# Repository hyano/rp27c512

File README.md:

# RP27C512

**RP27C512**は、[秋月電子通商](https://akizukidenshi.com/)の
[RP2040マイコンボードキット(AE-RP2040)](https://akizukidenshi.com/catalog/g/g117542/)を使用して、
EP-ROM(27C512)のエミュレーションを行うデバイスです。
このデバイスは、AE-RP2040のGPIOを27C512相当のDIP-28ピンアサインに変換する基板と、GPIOを制御するためのファームウェアで構成されています。

ROMのエミュレーションに加え、同一バス上のメモリやデバイスへのアクセスを監視・解析する機能も備えていることが特長です。

ROMデータ書き換えて機器やプログラムの動作確認をしたり、
メモリの内容やデバイスのアクセスを監視して機器の挙動を調べる用途を想定しています。

興味のある方がいらっしゃれば、基板やキットの頒布を検討しますので、お声掛けください。

## 概要

* 27C512の代わりに**RP27C512**を装着して、ROM機能をエミュレーションすることができます。
* /OE信号がアサートされてから約40nsでデータ出力が可能です。
* **RP27C512**をホスト(Windows PCやMac)に接続すると、USBシリアルポートとして認識されます。
* UARTターミナルを使って、コマンドラインインターフェースから各種操作が可能です。
* ROMデータはAE-RP2040のフラッシュメモリに最大4つまで保存でき、切り替えて使用できます。
* ホストからROMデータを**RP27C512**に転送できます。転送にはXMODEMを使用します。
* **RP27C512**に保存されたROMデータをホストに転送することが可能です。転送にはXMODEMを使用します。
* **RP27C512**をROM(27C512)に接続し、実チップからデータを直接読み出すことができます。
* **RP27C512**の基板を流用して、ROM(27C512)を**RP27C512**に接続するための子基板を作ることができます。
* バスアクセスの監視機能を備えており、同一バス上に接続されたメモリやデバイスへのアクセスを解析できます。
  * 書き込みデータを**RP27C512**のRAMに記録して、確認できます。機器のRAMの内容に相当します。
  * RAMのデータをXMODEMを使用してホストとの間で転送することが可能です。
  * 指定した領域へのアクセスを時系列で表示することができます。
* 3つの動作モードを備えます。
  * emulatorモード: ROMのエミュレーションとバスアクセスの監視をします。
  * snoopモード: バスアクセスの監視をします。
  * cloneモード: ROMの読み出しをします。

## ハードウェア

* [RP27C512/AE-RP2040変換基板](hardware/)は、AE-RP2040のピンアサインを27C512相当に変換するシンプルな基板です。
* 回路図や基板レイアウトはKiCadで作成しており、`hardware/`ディレクトリに格納しています。
* **<ins>AE-RP2040のGPIOは3.3Vで、27C512は5Vで駆動しますが、レベル変換回路は入れていません。
  作者の環境では正常に動作していますが、故障や想定外の動作について作者は責任を負いかねます。</ins>**
* RP2040を400MHzまでオーバークロックして使用しています。
* 27C512側の5V電源をAE-RP2040に供給することが可能です。ショットキーバリアダイオードで逆流防止を行っています。

### 信号の接続関係

|AE-RP2040|接続先|信号名|補足                             |
|---------|------|------|---------------------------------|
|GPIO0-15 |27C512|A0-15 |アドレスバス                     |
|GPIO16-23|27C512|DQ0-7 |データバス                       |
|GPIO27   |27C512|/CE   |チップイネーブル                 |
|GPIO28   |27C512|/OE   |出力イネーブル                   |
|GPIO29   |基板  |/WR   |4Pピンヘッダ1/書き込みイネーブル |
|GPIO24   |-     |(EXT0)|4Pピンヘッダ2/将来用             |
|GPIO25   |-     |(EXT1)|4Pピンヘッダ3/将来用             |
|GPIO26   |-     |(EXT2)|4Pピンヘッダ4/将来用             |
|GND      |27C512|VSS   |                                 |
|+5V      |27C512|VCC   |ショットキーバリアダイオード経由 |
|+3.3V    |-     |-     |                                 |

### 部品一覧

[RP27C512/AE-RP2040変換基板](hardware/)の他に必要になる部品の一覧です。
[秋月電子通商](https://akizukidenshi.com/)で揃える場合の例です。電気的に接続するだけなので、同等品で問題ありません。
子基板はsnoopモードとcloneモードでROMを接続しやすくするためのもので、ROMエミュレーションには必要ありません。

* 親基板(本体)
  * [RP2040マイコンボードキット](https://akizukidenshi.com/catalog/g/g117542/)
  * [ロープロファイルピンヘッダー(低オス) 1×40(40P) 9.54mm](https://akizukidenshi.com/catalog/g/g100171/)
    * 子基板を取り付けない場合は
      [ロープロファイルピンヘッダー(低オス) 1×40(40P) 7.7mm](https://akizukidenshi.com/catalog/g/g102900/)
      の方が見栄えがよいでしょう。
  * [丸ピンIC用連結ソケット 1×14 MH-1X14-L2](https://akizukidenshi.com/catalog/g/g116982/)
    * 秋葉原の店舗には常備していないようなので要注意です。
    * [丸ピンIC用連結ソケット 両端オスピン・1列14P](https://akizukidenshi.com/catalog/g/g100862/)のピンを切断して使っても、
      [細ピンヘッダー 1×40 (黒)](https://akizukidenshi.com/catalog/g/g106631/)を使ってもよいでしょう。
  * [ピンヘッダー (オスL型) 1×40 (40P)](https://akizukidenshi.com/catalog/g/g101627/)
  * [ショットキーバリアダイオード 45V2A SBM245L](https://akizukidenshi.com/catalog/g/g117439/)
    * 適当なもので構わないです。VFの小さな安価なものを使いました。
* 子基板(snoopモード・cloneモード用)
  * [シングルピンソケット (低メス) 1×20 (20P)](https://akizukidenshi.com/catalog/g/g103138/)
  * [ICソケット (28P) 600mil](https://akizukidenshi.com/catalog/g/g115763/)
  * スズメッキ線少々
    * 親基板のダイオードのリード線の残りなどで問題ないでしょう。

### 組み立て(親基板)

各部品を部品を基板にハンダ付けして取り付けます。
スペースが狭く、干渉するので、ハンダの量が多くなりすぎないように注意します。

* ショットキーバリアダイオードを基板に取り付けます。
  * USBケーブルからの電源のみで使用する場合は、必要はありません。
  * ダイオードの太さによってはAE-RP2040と接触します。作者は気にしていません。
* 丸ピンIC用連結ヘッダを基板に取り付けます。
  * ロープロファイルピンヘッダーとの距離が狭いため、両方を基板に固定した状態でハンダ付けするとよいです。
* ロープロファイルピンヘッダーを基板に取り付けます。
  * 9.54mmタイプを使用する場合は、足の長いピンが上方(AE-RP2040側)になる向きにします。
* L型ピンヘッダーを4P分に切断し、基板に取り付けます。
  * 先に取り付けてしまうと、樹脂部分が邪魔で、丸ピンIC用連結ヘッダの半田付けが難しくなります。
* ロープロファイルピンヘッダーにAE-RP2040を取り付けます。
  * 基板間が狭いので、スペースを残すためにQIコネクタを取り付けた状態でハンダ付けするとよいです。
  * 子基板を使用する場合、ハンダが上方に付着していると子基板のピンソケットに刺さりません。
    スルーホール付近にだけハンダが乗るようにします。多くつき過ぎた場合は、ハンダ吸い取り線で除去するのがよいです。

### 組み立て(子基板)

snoopモードとcloneモードでROMを接続しやすくするための基板です。

* スズメッキ線をダイオードの代わりにD1の位置に取り付けます。
* ICソケットを取り付けます。
  * 次に取り付けるシングルピンソケットも基板に固定した状態でハンダ付けするとよいです。
* シングルピンソケットを17P分に切断し、基板に取り付けます。

## ファームウェア

* このプログラムは[Raspberry Pi Pico-series C/C++ SDK](https://www.raspberrypi.com/documentation/pico-sdk/)でビルド可能です。
* ソースコードは`firmware/`ディレクトリに格納しています。
* ビルド後に生成される`rp27c512.uf2`を所定の方法で**RP27C512**に書き込み、使用します。

## ファームウェアのビルド

事前に Raspberry Pi Pico SDK をインストールし、下記のコマンドでビルドすることができます。

```sh
git clone https://github.com/hyano/rp27c512.git
cd rp27c512/firmware
mkdir build
cd build
cmake ..
make
cp rp27c512.uf2 /Volumes/RPI-RP2
```

## 使用方法

### ハードウェアの取り付け

* emulatorモードで使用する場合、基板のICソケットからROM(27C512)を外し、代わりに**RP27C512**を取り付けます。その他のモード、詳細は、以降の各モードの説明を参照して下さい。
* 書き込みアクセスをキャプチャする場合は、基板下側の4Pピンヘッダのうち、シルクが白く塗りつぶされたピンを/WR信号に接続します。
* ホストとUSBケーブルで接続すると、USBシリアルポートとして認識されます。
* USBケーブルを接続しなくても基板側の電源で動作しますが、**RP27C512**の起動時間が必要なため、接続先の機器の起動に間に合わないかもしれません。
* 基板下側のピンヘッダの残り3Pは将来拡張用です。他の信号キャプチャや、機器のリセットなどの制御に使用することを検討しています。

### コマンドラインインタフェース

**RP27C512**をホストとUSBケーブルで接続すると、USBシリアルポートとして認識されます。
UARTターミナルを使って、コマンドラインインターフェースから各種コマンドを使用して操作することができます。

|コマンド|引数|説明|モード|
|-|-|-|-|
|help, ?|-|ヘルプを表示する。|e/s/c|
|hello|any...|コマンドラインの動作確認用。与えられた引数を表示する。|e/s/c|
|cls|-|画面をクリアする。|e/s/c|
|reboot|[delay]|再起動する。delayで再起動までの秒数を指定可能。|e/s/c|
|mode|"emulator"\|"snoop"\|"clone"|ROMエミュレーションを行うemulatorモード、アクセスの解析のみを行うsnoopモード、ROMの読み出しを行うcloneモードを切り替える。modeはFLASH ROMに保存される。コマンド実行完了後、自動的に再起動する。|e/s/c|
|bootsel|[delay]|RP2040をBOOTSELモードで再起動する。|e/s/c|
|gpio|-|GPIOの状態と設定を表示する。|e/s/c|
|gpio|"in"\|"out" pin|GPIOを入力か出力を設定する。(ext0-2のみに有効)|e/s/c|
|gpio|"pullup"\|"pulldown"\|"pullno" pin|GPIOをプルアップ/プルダウン/どちらもなしを設定する。|e/s/c|
|gpio|"set"\|"clr" pin|GPIOの値を設定する。(ext0-2のみに有効)|e/s/c|
|gpio|"pulse" pin [width]|GPIOの値を一定期間反転する。width[us]でパルス幅を指定する(defaultは100us)。(ext0-2のみに有効)|e/s/c|
|gpio|"save"|FLASH ROMにGPIOの設定を保存する。|e/s/c|
|device|"rom"\|"ram"|操作対象のデバイスをROMかRAMで切り替える。ダンプ、データ転送に影響する。|e/s/-|
|d|[addr]|デバイス上のデータを指定したアドレスから16進ダンプする。アドレスを省略すると前回の続きをダンプする。|e/s/c|
|dw|[addr]|何かキーが押されるまで、16進ダンプを繰り返す。RAM上のデータの変化を目視するために使う。|e/s/-|
|dlen|len ["save"]|16進ダンプする時の表示行数を設定する。数値の後にsaveオプションをつけると設定をFLASH ROMに保存する。|e/s/c|
|e|[addr [value]]|デバイス上のデータを編集する。アドレスを省略すると前回の続きを編集する。値を省略すると対話型で入力になる。|e/s/c|
|m|start end dest|デバイス上のデータを移動する。|e/s/c|
|f|start end value|デバイス上の指定範囲を指定した値で埋める。|e/s/c|
|watch|start end|指定したアドレス範囲をcapコマンドでキャプチャするよう設定する。|e/s/-|
|unwatch|start end|指定したアドレス範囲をcapコマンドでキャプチャしないよう設定する。|e/s/-|
|cap|-|設定したアドレス領域へのアクセスを時系列に従って表示する。|e/s/-|
|wlist|[start [end]]|capコマンドでキャプチャする範囲を表示する。start、endで表示する範囲を指定できる。|e/s/-|
|wsave|-|capコマンドでキャプチャする範囲を保存する。|e/s/-|
|recv|-|ホストからデバイスにデータを転送する。64KiBのバイナリデータをXMODEM(CRC)で転送する。|e/s/c|
|send|-|デバイスからホストにデータを転送する。64KiBのバイナリデータをXMODEM(1K)で転送する。|e/s/c|
|bank|0\|1\|2\|3|使用するFLASH ROMのバンクを指定する。バンクの指定はFLASH ROMに保存され、次回起動時はそのバンクからROMデータを読み出す。|e/s/c|
|load|-|FLASH ROMからデータを読み出す。bankコマンドで指定したバンクを使用する。|e/s/c|
|save|-|FLASH ROMにデータを保存する。bankコマンドで指定したバンクを使用する。|e/s/c|
|erase|0\|1\|2\|3|FLASH ROMのデータを消去する。バンク番号を明示的に指定する。|e/s/c|
|clone|[wait [verify]]|直接接続した27C512からデータを読み出す。読み出し開始までの秒数(wait)と、ベリファイ回数(verify)を指定できる。|-/c|
|init|"all"\|"rom"\|"config"|FLASH ROMのデータ、設定を初期化する。設定を初期化する場合は、自動的に再起動する。|e/s/c|

* モードはe(emulatorモード)、s(snoopモード)、c(cloneモード)を示します。
* [arg]は省略可能な引数を表します。
* FLASH ROMにアクセスするコマンドを実行すると、動作クロック周波数を一時的に下げるためにROMエミュレーションが乱れます。
* gpioコマンドのピン指定は番号の他に信号名も使えます。(a0-a15,d0-d7,ce,oe,wr,ext0-ext2)
* 引数のチェックはほとんどしていないので、不正な引数を指定するとすぐに暴走します。

### emulatorモード

emulatorモードは、**RP27C512**をROM(27C512)の代わりに動作させるモードです。
`mode emulator`コマンドでemulatorモードに切り替わります。

emulatorモードでは、ROMを基板のICソケットから取り外し、代わりに**RP27C512**を取り付けます。
ROMが基板直付けの場合は、ICソケットを取り付けると良いでしょう。

書き込みアクセスをキャプチャするには、基板下側の4Pピンヘッダのうち、シルクが白く塗りつぶされたピンを/WR信号に接続します。

**RP27C512**の起動時にFLASH ROMからROMデータが読み出され、すぐにROMのエミュレーションが開始されます。

ROMデータは、USBターミナルソフトからXMODEMで転送するか、後述のcloneモードで実チップから読み出すかで、
あらかじめ**RP27C512**のFLASH ROMに保存しておきます。
FLASH ROMアクセス中は、**RP27C512**の動作クロック周波数を下げる必要があるため、ROMのエミュレーション速度が落ちます。
基板から取り外すか、基板の電源を切った状態で作業すると良いでしょう。

### snoopモード

snoopモードは、emulatorモードからROMのエミュレーションを停止させたモードです。
オリジナルのROMを使いつつ、バスのアクセスを監視する場合に使います。
`mode snoop`コマンドでsnoopモードに切り替わります。

snoopモードでは、ROMと基板の間に**RP27C512**を取り付けます。
**RP27C512**に子基板を取り付け、そのICソケットにオリジナルのROMを取り付けると良いでしょう。

### cloneモード

cloneモードは、**RP27C512**を直接ROM(27C512)の実チップに接続して、データを読み出すモードです。
`mode clone`コマンドでcloneモードに切り替わります。

子基板を使用する場合は、子基板にROMを取り付け、子基板を**RP27C512**に上から接続します。
ROMの電源はUSBポートから供給されます。

子基板を使用しない場合は、ROMに上から被せる形で**RP27C512**を乗せ、ピン同士を接触させます。
**RP27C512**を直接被せるのではなく、平ピン型のICソケットを間に挟むと、より接触させやすいです。
ROMの電源は外部から供給しても良いですし、**RP27C512**のショットキーバリアダイオードをバイパスしてUSBポートから供給しても良いでしょう。

接続ができたら、`clone`コマンドで実チップからデータを読み出します。
読み出しに成功したら、`save`コマンドでFLASH ROMに保存して、`mode emulator`でemulatorモードに戻しておきます。

**RP27C512**内のROMデータは、XMODEMでホスト側に転送することもできますので、簡易ROMリーダとしても使用することができます。

```sh
> mode clone
mode: clone
rebooting...

connected.
RP27C512 VER1.00
rom bank: 0
mode: clone
> clone
read ROM
 wait  : 5 s
 verify: 2 times
read start ... done.
verify (1/2) ... OK
verify (2/2) ... OK
clone: OK
> bank 0
current rom bank: 0
> save
save: OK
> mode emulator
mode: emulator
rebooting...

connected.
RP27C512 VER1.00
rom bank: 0
mode: emulator
> 
```

## ROMエミュレーションの実装

ROMエミュレーションは、データ出力部とバス制御部から構成されます。
アドレスバス(A0-A15)と制御信号(, /OE)の状態に応じて、データバス(D0-D7)に値を出力します。

### データ出力部

データ出力部は、アドレスバス(A0-A15)で指定されたアドレスに対応するROMイメージのデータを、データバス(D0-D7)に設定します。
PIOステートマシン1つ(SM)と、DMAを2チャネル(DMA0, DMA1)使用して実現しています。

* SMには、ROMイメージの配列変数の先頭アドレスの上位16ビットを転送して初期化します。
  * ROMイメージの配列変数は64KiBにアラインメントしておきます。
* SMは、GPIO(A0-A15)を読み出し、アクセス先のアドレスを合成し、FIFOに送信します。
* DMA0はSMのFIFOを監視するように設定しておき、SMからアドレスが送られてきたら、DMA1にそのアドレスからデータ転送を指示します。
* DMA1は、DMA0から指示されたアドレスからデータを読み出し、SMのFIFOに書き込みます。
* SMはDMA1から送られてきたデータをGPIO(D0-D7)に出力します。
* 上記を繰り返します。

### バス制御部

バス制御部は、制御信号(/CE, /OE)を監視し、データバス(D0-D7)を出力状態を制御します。
PIOステートマシン1つで実現しています。

* SMは、GPIO(/CE, /OE)の値を確認します。
* 両方が0の場合は、GPIO(D0-D7)を出力モードに切り替えます。
* そうでない場合は、GPIO(D0-D7)を入力モード(ハイインピーダンス)に切り替えます。
* 上記を繰り返します。

## バスアクセス監視の実装

バスアクセス監視は、書き込みデータ取り込み部とアクセスデータキャプチャ部から構成されます。

### 書き込みデータ取り込み部

書き込みデータ取り込み部は、書き込みアクセスがあると、アドレスバス(A0-A15)で指定されたRAMイメージのアドレスに、
データバス(D0-D7)の値を書き込みます。
PIOステートマシン1つ(SM)とDMAを2チャネル(DMA0, DMA1)使用して実現しています。

* SMには、ROMイメージの配列変数の先頭アドレスの上位16ビットと、
  0~256をあらかじめ書き込んだ値データの配列変数の先頭アドレスの上位24ビットを転送して初期化します。
  * RAMイメージの配列変数は64KiBにアラインメントしておきます。
  * 値データの配列変数は256Bにアラインメントしておきます。
* SMは、GPIO(/WR)の立ち上がりを待ち、その時のGPIOの値をキャプチャします。
* SMは、GPIO(D0-D7)の値から値データのアドレスを合成し、FIFOに送信します。
* SMは、GPIO(A0-A15)の値からRAMアクセス先のアドレスを合成し、FIFOに送信します。
* DMA0はSMのFIFOを監視するように設定しておき、SMからアドレス二つが送られてきたら、DMA1にそのアドレス間のデータ転送を指示します。
* DMA1は、DMA0から指示された値データのアドレスからデータを読み出し、RAMイメージのアドレスに書き込みます。
* 上記を繰り返します。

### アクセスデータキャプチャ部

アクセスデータキャプチャ部は、制御信号(/WR, /OE)を監視し、変化があるとその内容を64エントリのリングバッファに取り込みます。
PIOステートマシン1つ(SM)とDMAを2チャネル(DMA0, DMA1)使用して実現しています。

* SMは、GPIO(/WR, /OE)を確認します。
* 両方が1に変化した時、その時のGPIO(A0-A15, D0-D7, EXT0-EXT2, /CE)の値と直前のGPIO(/WR, /OE)の値を合成して、FIFOに送信します。
* DMA1は、SMから送られてきたデータをリングバッファに書き込みます。
  * リングバッファは、256Bにアラインメントしておきます。
  * リングバッファのどこまで書き込んだかは、DMAの書き込み先アドレスを確認することで知ることができます。
* リングバッファの終端に到達すると、DMA1は転送を終了して、DMA0をトリガします。
* DMA0は、DMA1の転送先アドレスをリングバッファの先頭に設定して、DMA1を再起動します。
* 上記を繰り返します。

## デモ動画

Roland CM-32PのROMを**RP27C512**で置き換え、
X68000版 闇の血族(1990 システムサコム)のBGM(CM-64向け)を演奏した時のRAMの内容のダンプ、
PCMデバイスへのアクセスの監視をしている様子をデモとして録画したものです。

https://github.com/user-attachments/assets/20a8eae4-5df2-4a57-8465-a8b28be44191

## 注意事項

* 作者の手元のごく少数の機器でのみ動作確認しています。すべての機器での動作を保証することはできません。
* 作者は、本デバイスの使用による一切の損害について責任を負いかねます。使用は使用者の責任で行ってください。

## 利用しているオープンソースソフトウェア

* [XMODEM implementation](https://github.com/Thuffir/xmodem)
  * Copyright 2001-2019 Georges Menie (www.menie.org)
  * Modified by Thuffir in 2019
* [Micro Read Line library for small and embedded devices with basic VT100 support](https://github.com/dimmykar/microrl-remaster)
  * Author: Eugene Samoylov aka Helius (ghelius@gmail.com) 01.09.2011
  * Remastered by: Dmitry Karasev aka dimmykar (karasevsdmitry@yandex.ru) 27.09.2021

## 参考文献・ソフトウェア

* [PicoROM: An RP2040-based ROM emulator](https://github.com/wickerwaka/PicoROM)
* [picoROM_pio: PIO/DMA implementation of picoROM project to simulate an EEPROM using a Raspberry Pico](https://github.com/rhulme/picoROM_pio)
* [Raspberry Pi Pico-series C/C++ SDK](https://datasheets.raspberrypi.com/pico/raspberry-pi-pico-c-sdk.pdf)
* [RP2040 Datasheet](https://datasheets.raspberrypi.com/rp2040/rp2040-datasheet.pdf)

## ライセンス

このソフトウェアは[MITライセンス](LICENSE)にて提供しています。  
Copyright (c) 2024 Hirokuni Yano

利用しているオープンソースソフトウェアは、そのライセンスに従います。

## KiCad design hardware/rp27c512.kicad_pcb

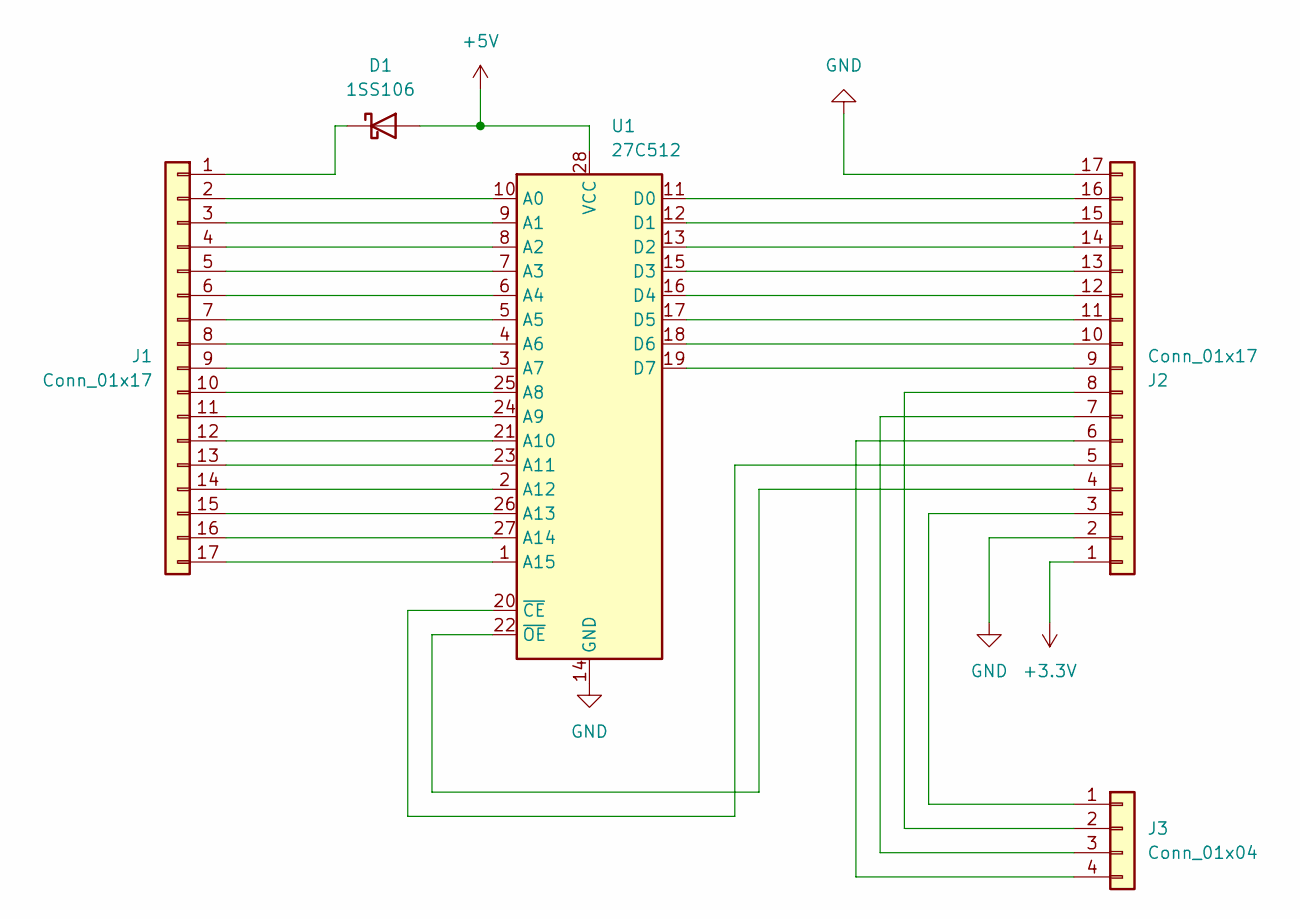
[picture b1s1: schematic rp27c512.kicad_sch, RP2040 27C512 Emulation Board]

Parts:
D1: 1SS106; D_DO-35_SOD27_P7.62mm_Horizontal
J1, J2: Conn_01x17; PinHeader_1x17_P2.54mm_Vertical
J3: Conn_01x04; PinHeader_1x04_P2.54mm_Horizontal
U1: 27C512; DIP-28_W15.24mm

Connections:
+3.3V: J2.1
+5V: D1.2 (A), U1.28 (VCC)
GND: J2.2, J2.17, U1.14 (GND)
unnamed: D1.1 (K), J1.1
unnamed: J1.2, U1.10 (A0)
unnamed: J1.3, U1.9 (A1)
unnamed: J1.4, U1.8 (A2)
unnamed: J1.5, U1.7 (A3)
unnamed: J1.6, U1.6 (A4)
unnamed: J1.7, U1.5 (A5)
unnamed: J1.8, U1.4 (A6)
unnamed: J1.9, U1.3 (A7)
unnamed: J1.10, U1.25 (A8)
unnamed: J1.11, U1.24 (A9)
unnamed: J1.12, U1.21 (A10)
unnamed: J1.13, U1.23 (A11)
unnamed: J1.14, U1.2 (A12)
unnamed: J1.15, U1.26 (A13)
unnamed: J1.16, U1.27 (A14)
unnamed: J1.17, U1.1 (A15)
unnamed: J2.3, J3.1
unnamed: J2.4, U1.22 (~OE)
unnamed: J2.5, U1.20 (~CE)
unnamed: J2.6, J3.4
unnamed: J2.7, J3.3
unnamed: J2.8, J3.2
unnamed: J2.9, U1.19 (D7)
unnamed: J2.10, U1.18 (D6)
unnamed: J2.11, U1.17 (D5)
unnamed: J2.12, U1.16 (D4)
unnamed: J2.13, U1.15 (D3)
unnamed: J2.14, U1.13 (D2)
unnamed: J2.15, U1.12 (D1)
unnamed: J2.16, U1.11 (D0)

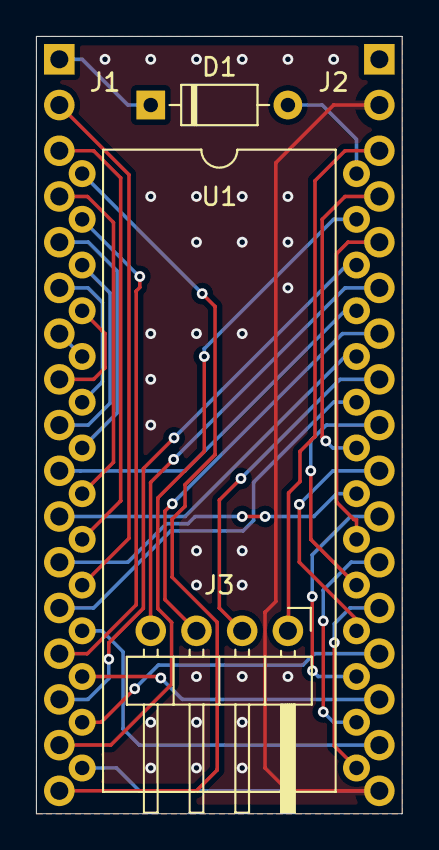
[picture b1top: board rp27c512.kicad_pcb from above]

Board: 2 copper layers, 20.3 x 43.2 mm, 5 parts (0 on the bottom side), 33 nets.

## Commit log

2024-10-26 added .gitignore
2024-10-26 panel data
2024-10-27 added .DS_Store
2024-10-27 added comment
2024-10-27 added gerber files
2024-11-02 added pin names
2024-11-02 added firmware
2024-11-02 added README
2024-11-02 change bank command order
2024-11-02 fixed rom_load/save() for ROM only
2024-11-02 fixed typo
2024-11-02 remove unneeded old line.
2024-11-02 added erase command
2024-11-02 added static for local functions.
2024-11-02 update hardware part in README
2024-11-02 use DMA for loading from flash rom
2024-11-02 use 250MHz for normal clock frequency
2024-11-02 no initialization for RAM/ROM
2024-11-03 update README for emulator mode
2024-11-04 start fixing copy_to_ram
2024-11-04 fixed copy_to_ram and make some variables uninitialized
2024-11-04 overclocking
2024-11-04 clean up
2024-11-04 cleanup
2024-11-04 added init command
2024-11-04 added init command to README
2024-11-04 change macro name from PULL_UP to DEBUG_PULL_UP
2024-11-04 added implementation memo
2024-11-08 fixed config_save before boot
2024-11-08 fixed schottky diode part no
2024-11-08 added dlen command
2024-11-08 fixed help for bank command
2024-11-08 added description for sub-board for clone mode
2024-11-08 added save option for dlen command
2024-11-09 add dlen command
2024-11-09 added alternative parts for connecting pin socket
2024-11-09 added images
2024-11-10 make cursor invisible during dump watch
2024-11-15 support capture area settings
2024-11-15 added mode bootsel feature
2024-11-15 unified signal names
2024-11-15 description for capture area settings
2024-11-15 added bootsel command
2024-11-15 added wlist command
2024-11-15 added link to Akizuki-denshi, etc
2024-11-16 use CMAKE_CURRENT_LIST_DIR
2024-11-16 16bit mask for address
2024-11-16 extended gpio command
2024-11-16 change signale name from CS to CE
2024-11-16 dump diff on verify error in clone mode
2024-11-16 added ASCII dump
2024-11-16 added edit command
2024-11-16 added move command
2024-11-16 added fill command
2024-11-16 added edit/move/fill command
2024-11-16 update gpio command help message
2024-11-16 emphasize about voltage level conversion
2024-11-16 refine GPIO debug code
2024-11-16 added snoop mode
2024-11-16 fixed help message for bank command
2024-11-16 added cls command
2024-11-16 cleanup command help
2024-11-16 restart shell if terminal disconnected
2024-11-16 added demo movie
2024-11-16 fixed URL of movie
2024-11-16 use iframe for youtube movie
2024-11-16 remove div tag
2024-11-16 not use HTML tag
2024-11-16 attached video
2024-11-16 replace video
2024-11-16 added explanation for video
2024-11-17 moved LICENSE to top directory
2024-11-17 fixed command-line for building firmware
2024-11-17 update references
2024-11-22 added GitHub Actions workflow
2024-11-22 fixed build parameter
2024-11-22 fixed directory name
2024-11-22 fixed PICO_SDK_PATH
2024-11-22 chaned archive name
2024-11-22 handle ^L as screen clear
